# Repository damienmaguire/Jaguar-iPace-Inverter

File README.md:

# Jaguar-iPace-Inverter
Design of Opensource Logic boards to run the Jaguar iPace Inverter and Motors.

PCB Designs in Kicad 9 format.

Front inverter used in the iPace is acuallly a Vitesco EPF2.8+ :
https://vitesco-technologies.com/en/Home/Solutions/Products/High-Voltage-Inverter-(EPF2-8-)-en

Reverse engineering thread on the openinverter forum :
https://openinverter.org/forum/viewtopic.php?f=23&t=1210

Videos :
https://youtu.be/Kg5qWuOF9P8

10/10/25 : Add prelim front drive unit V1 board design (work in progress).

25/03/26 : PCB Layout in progress.

28/03/26 : Layout done. First prototypes ordered from JLCPCB.

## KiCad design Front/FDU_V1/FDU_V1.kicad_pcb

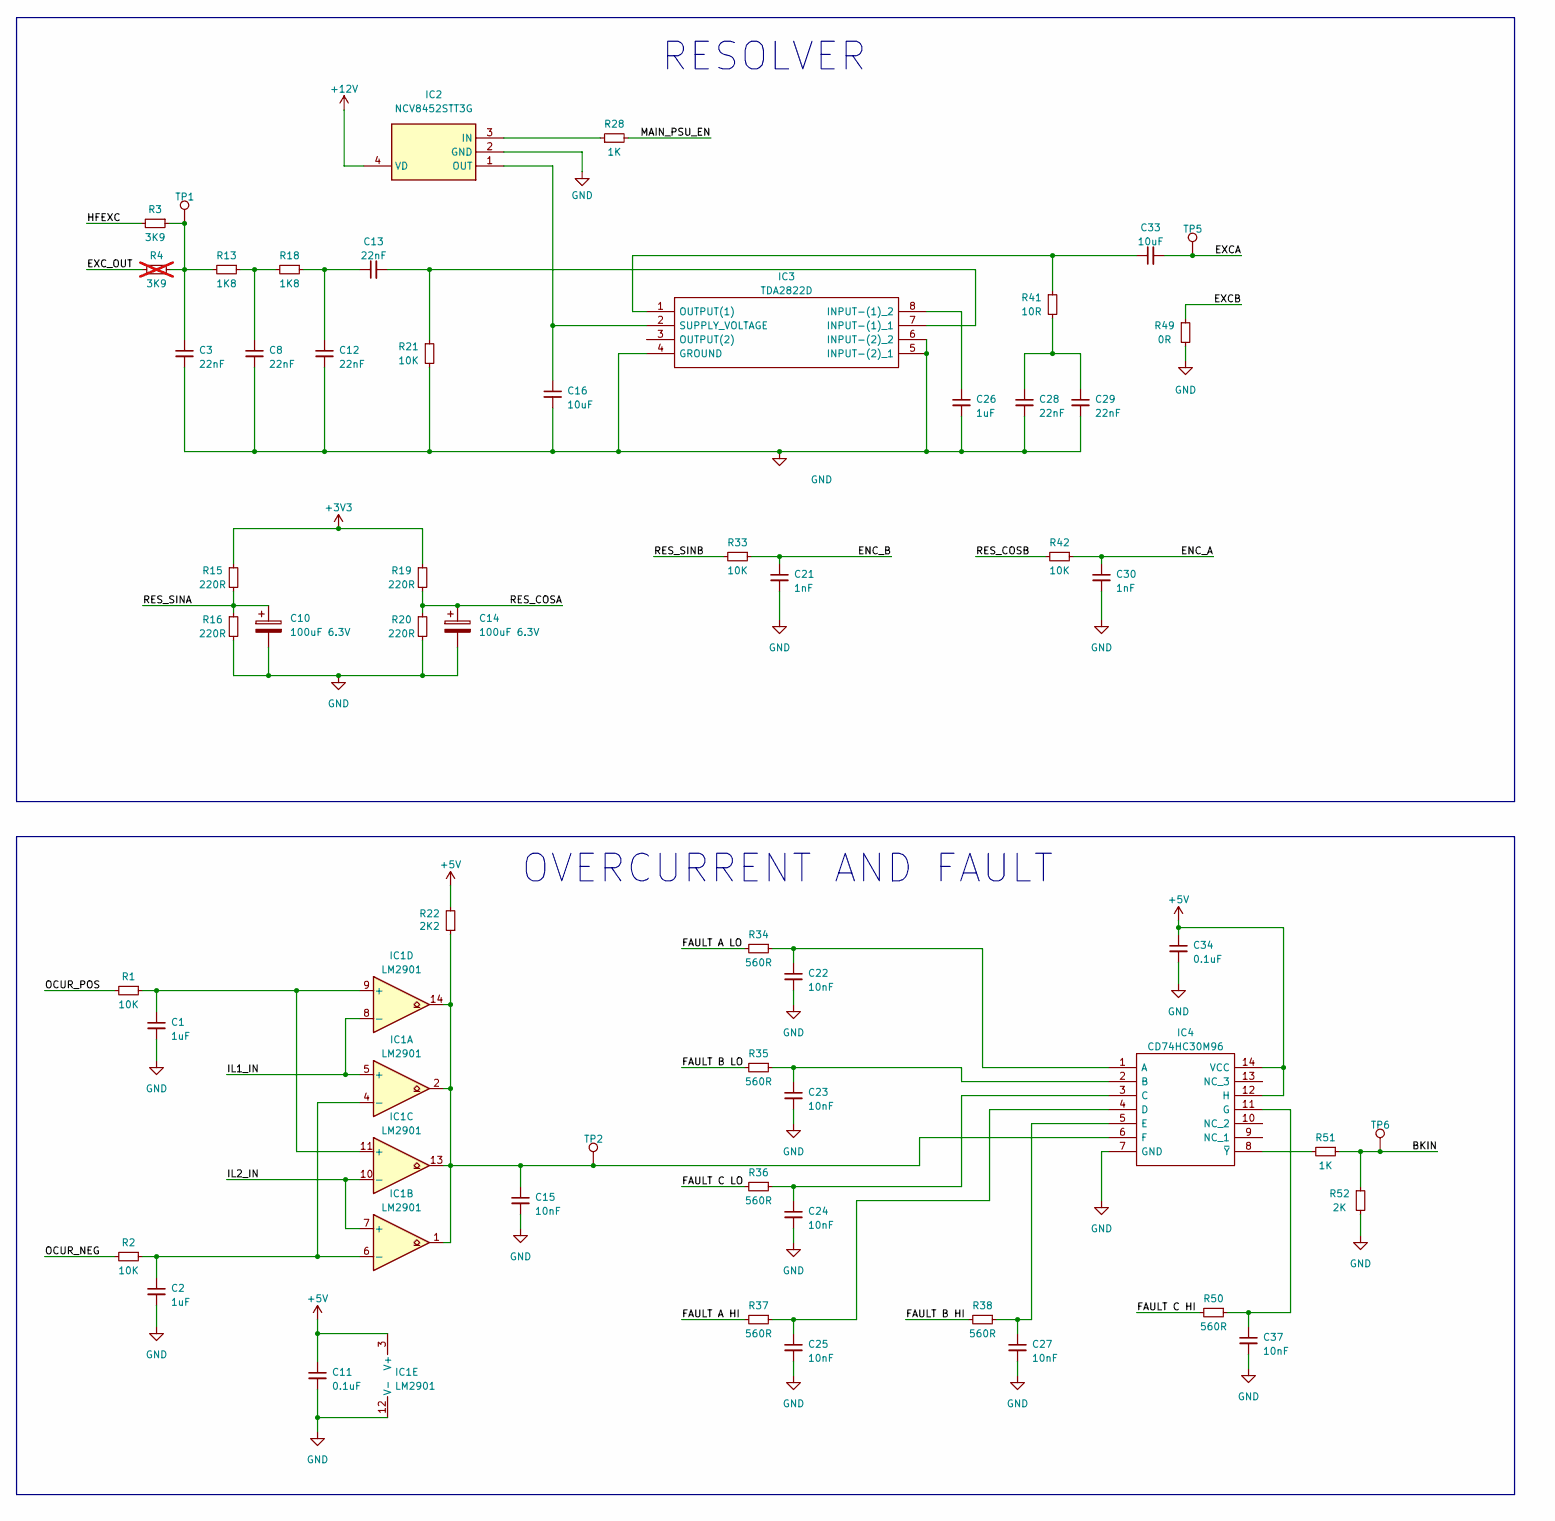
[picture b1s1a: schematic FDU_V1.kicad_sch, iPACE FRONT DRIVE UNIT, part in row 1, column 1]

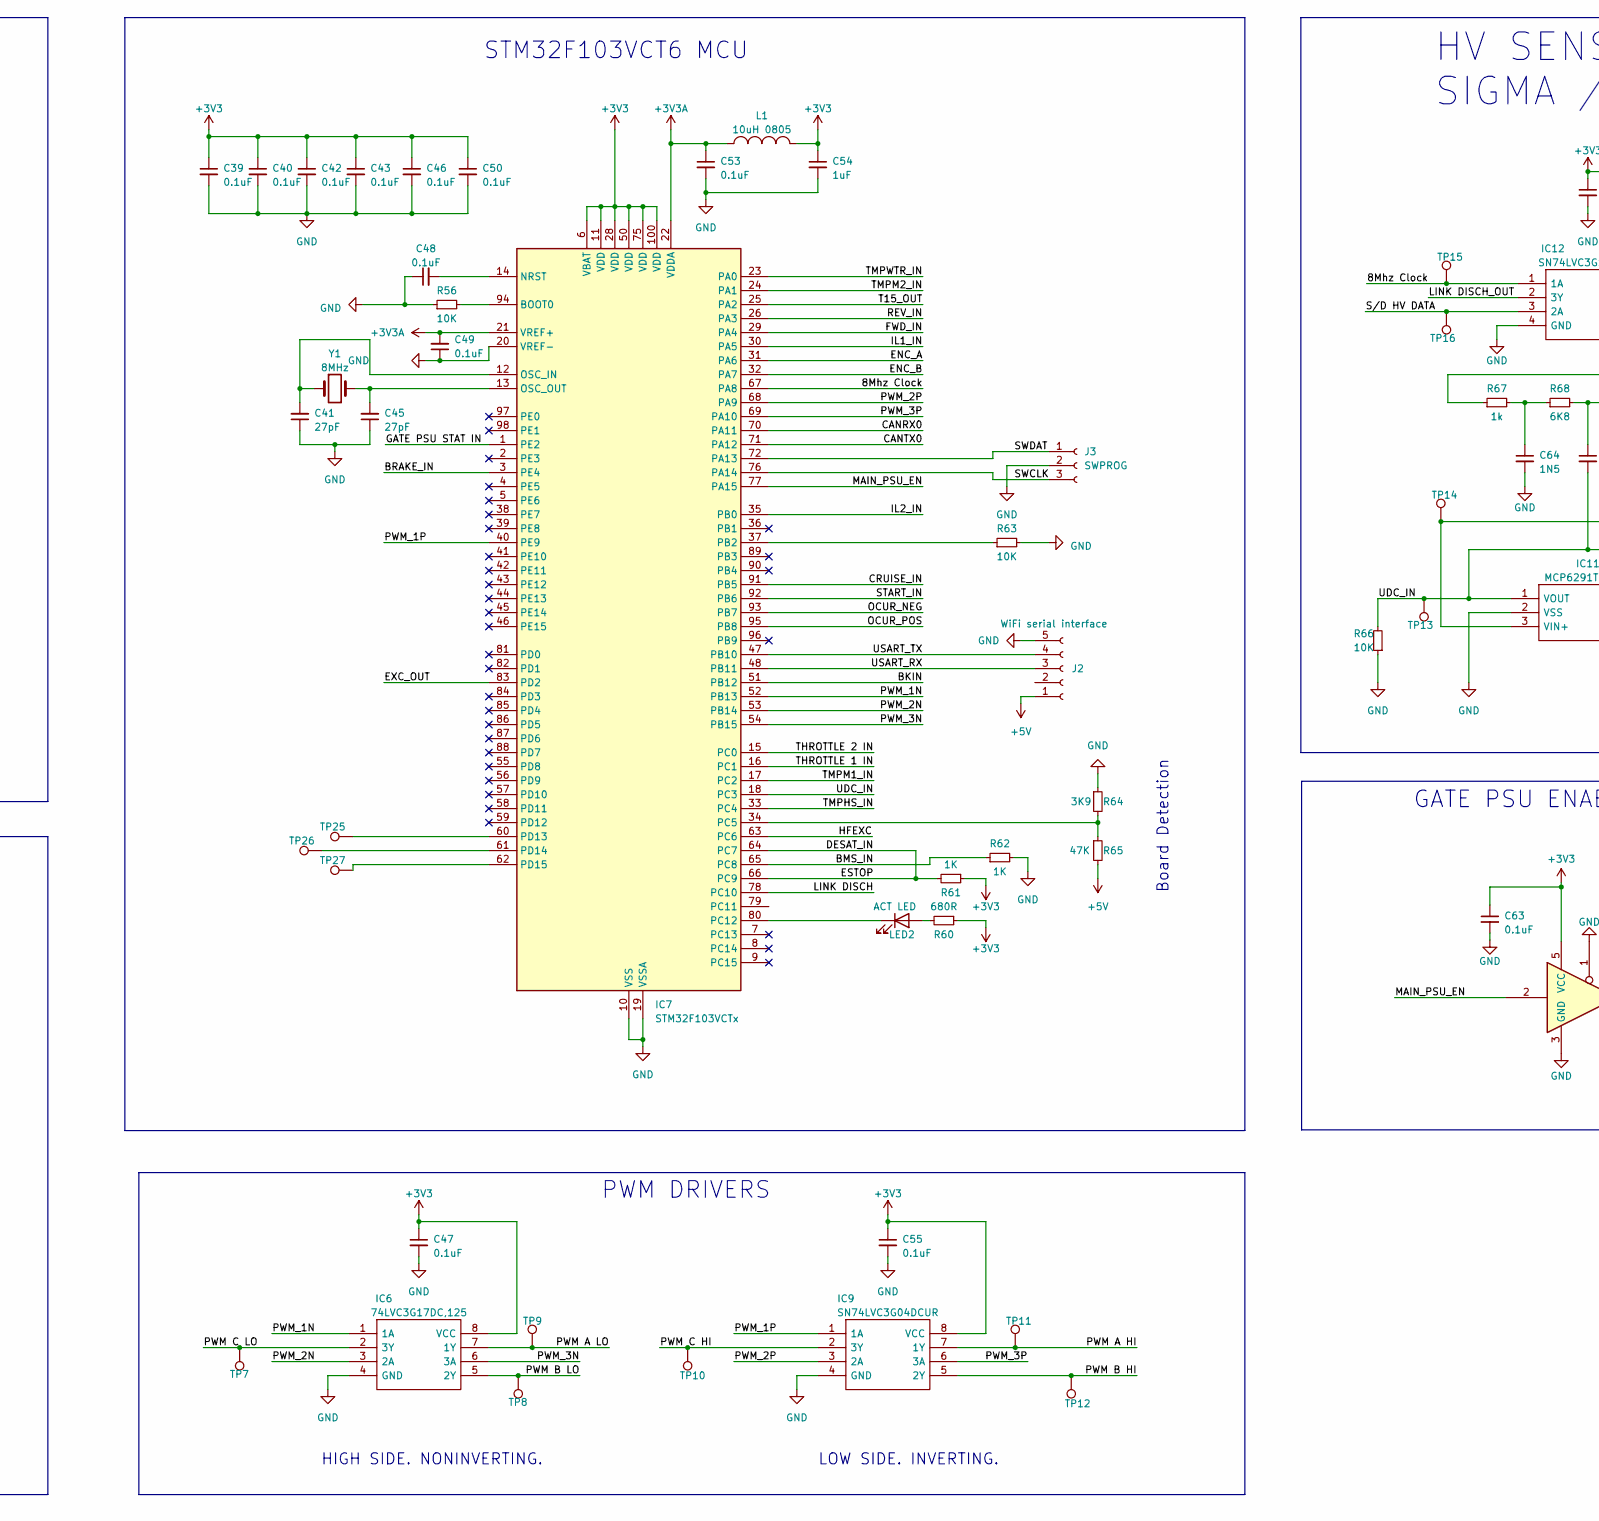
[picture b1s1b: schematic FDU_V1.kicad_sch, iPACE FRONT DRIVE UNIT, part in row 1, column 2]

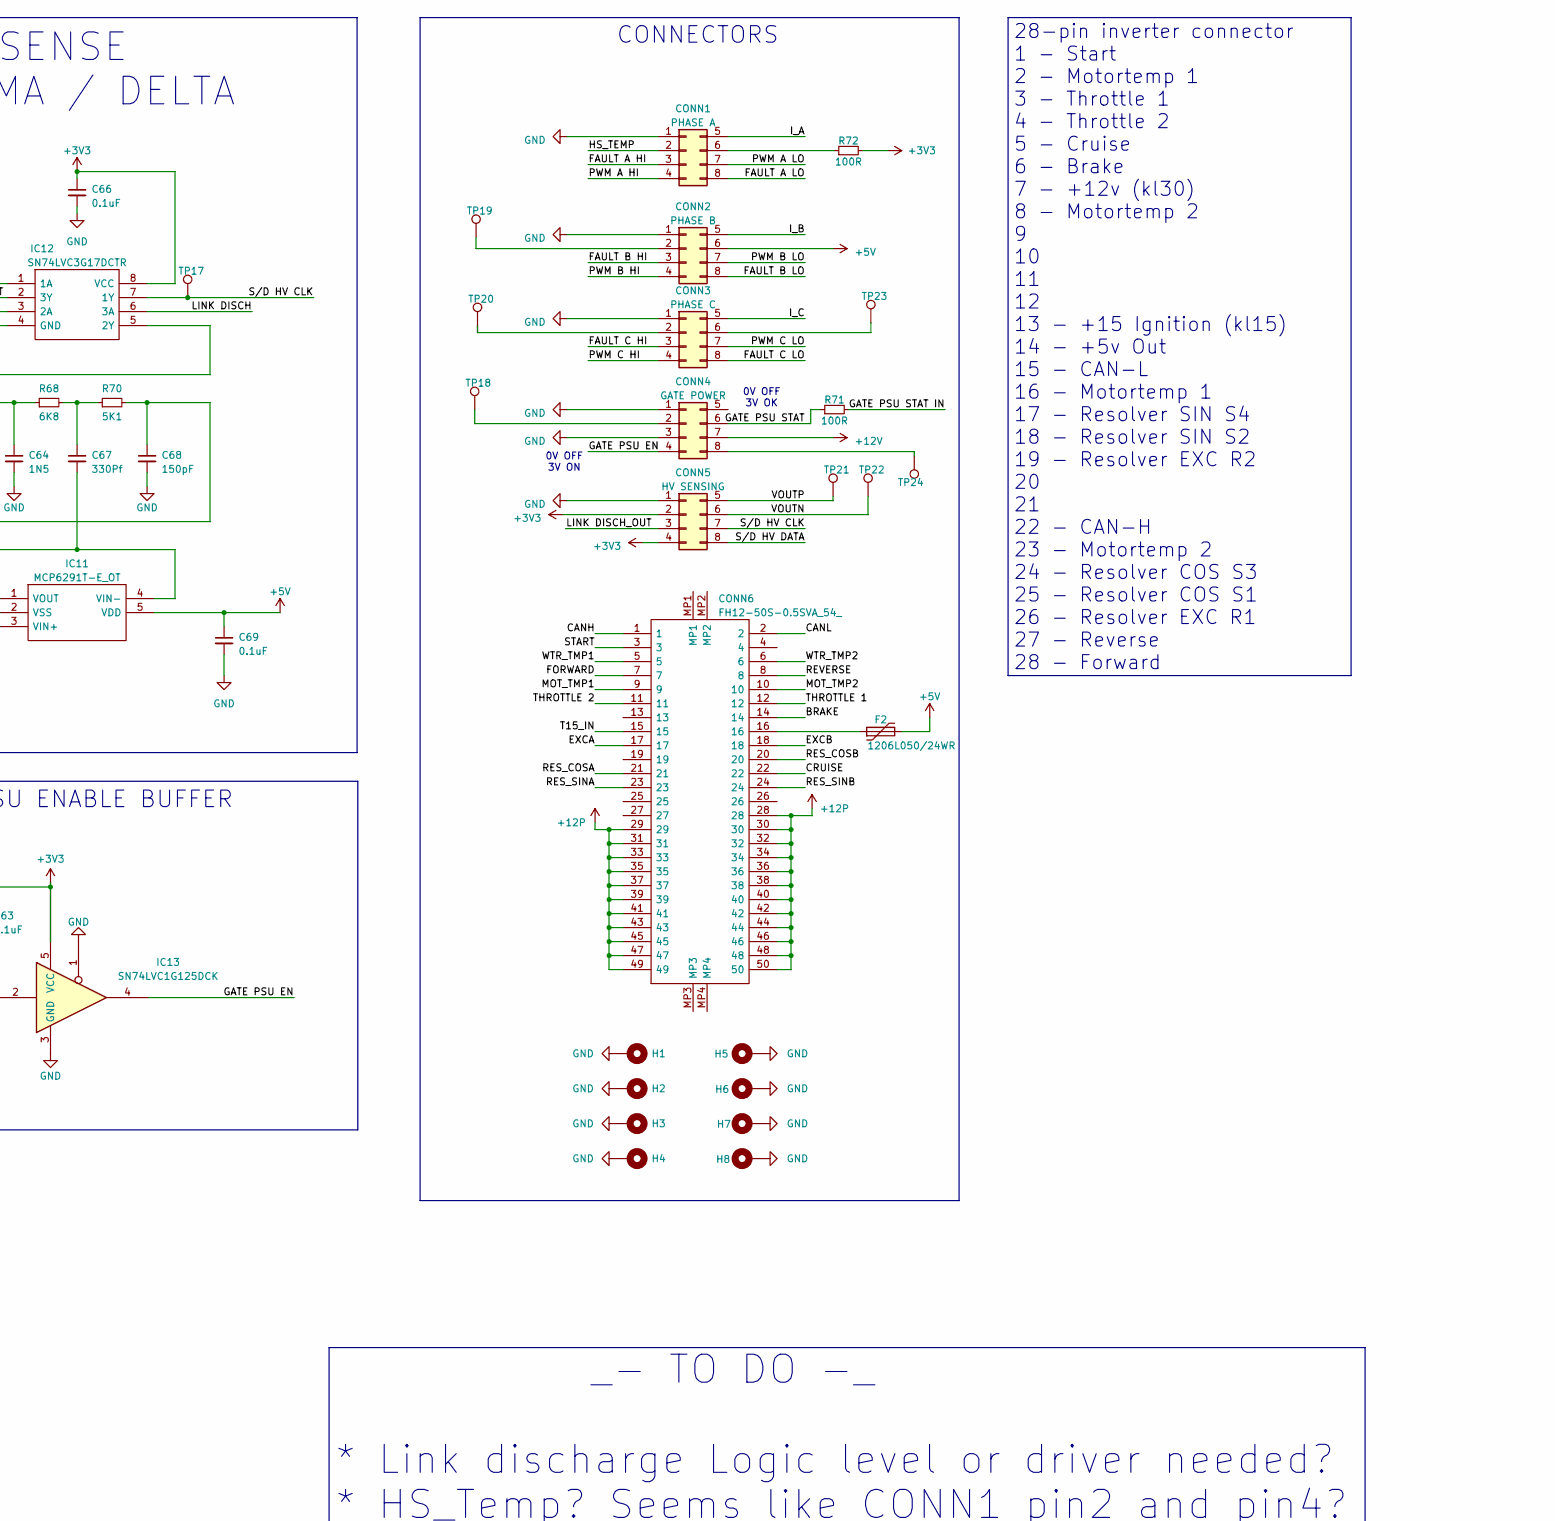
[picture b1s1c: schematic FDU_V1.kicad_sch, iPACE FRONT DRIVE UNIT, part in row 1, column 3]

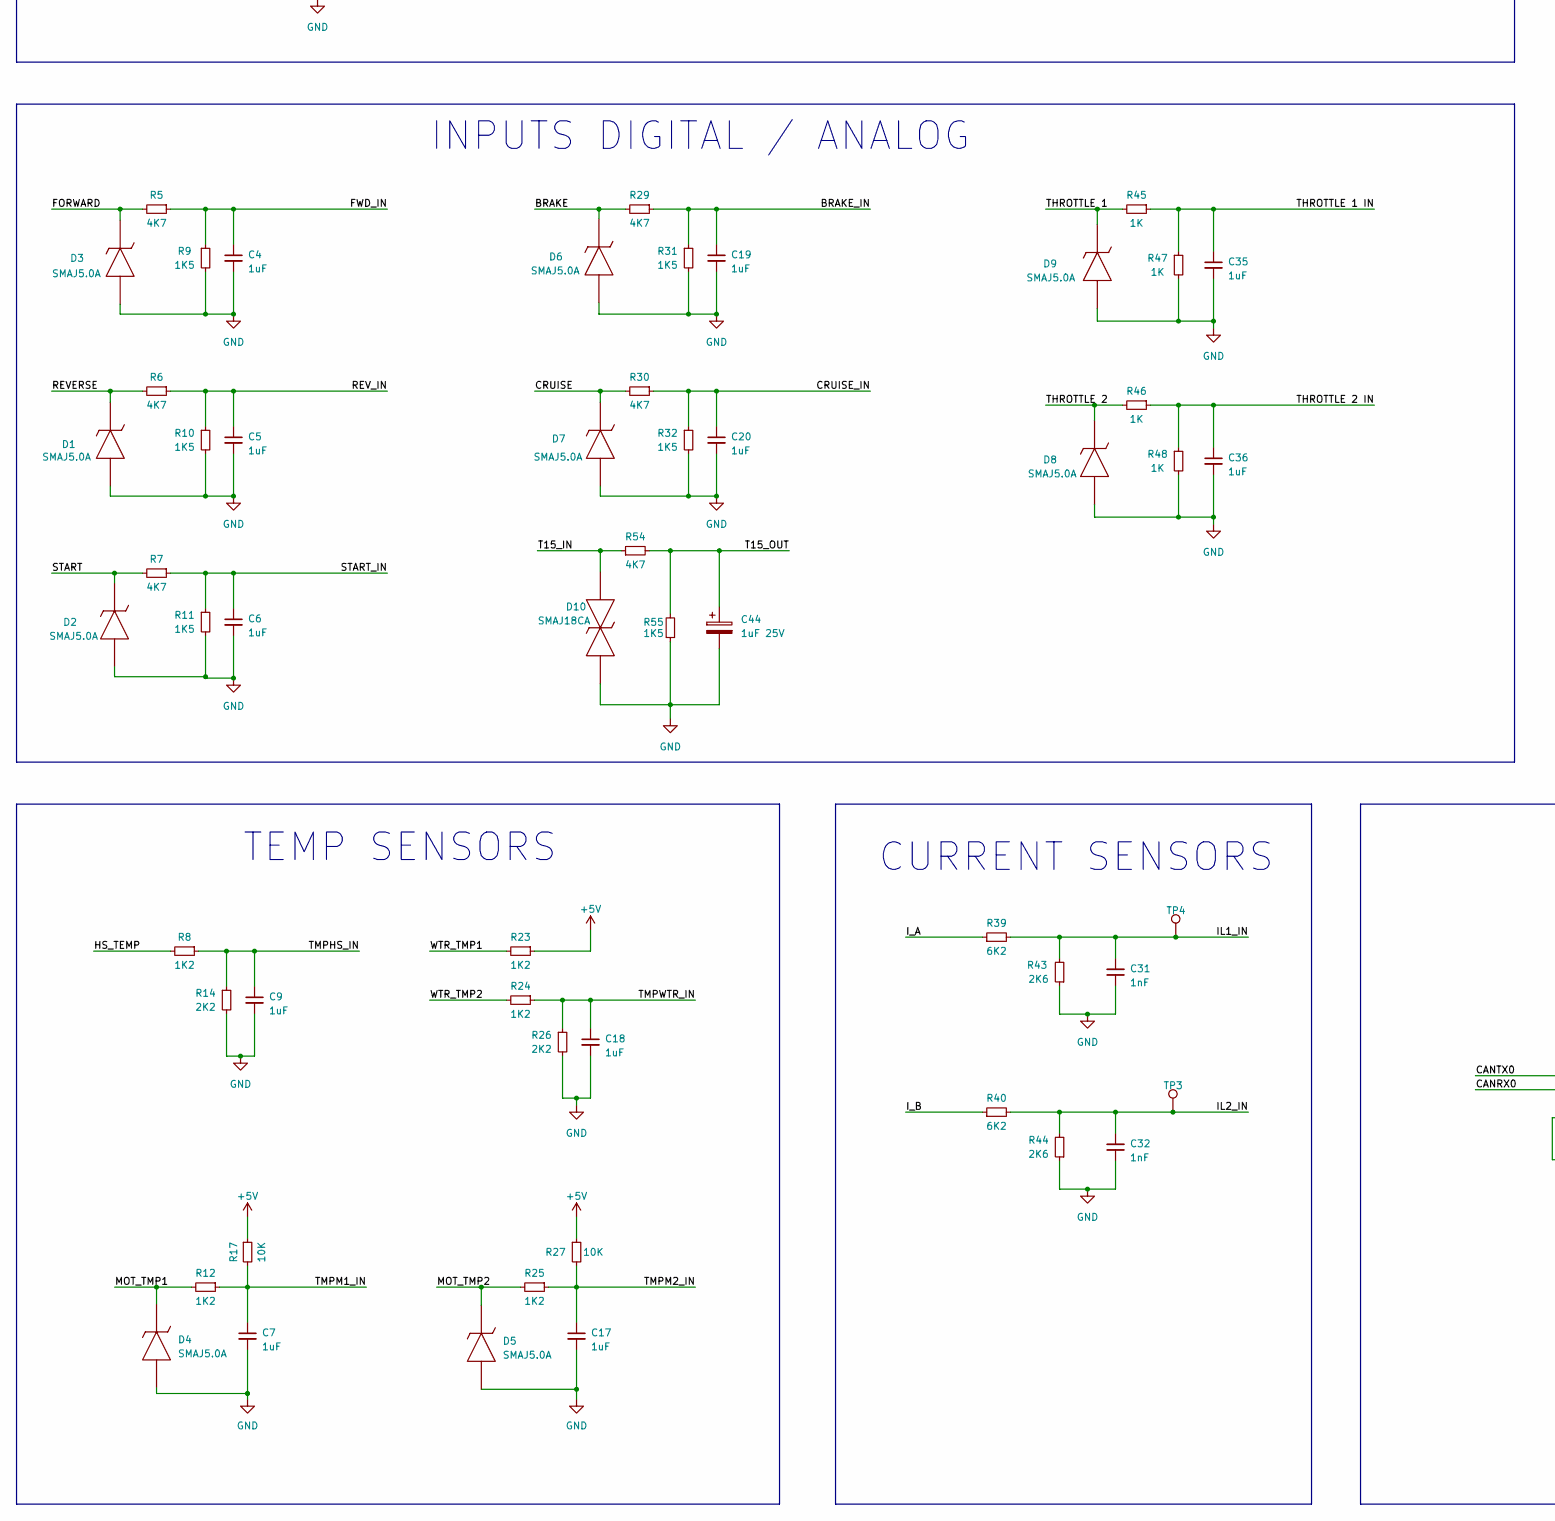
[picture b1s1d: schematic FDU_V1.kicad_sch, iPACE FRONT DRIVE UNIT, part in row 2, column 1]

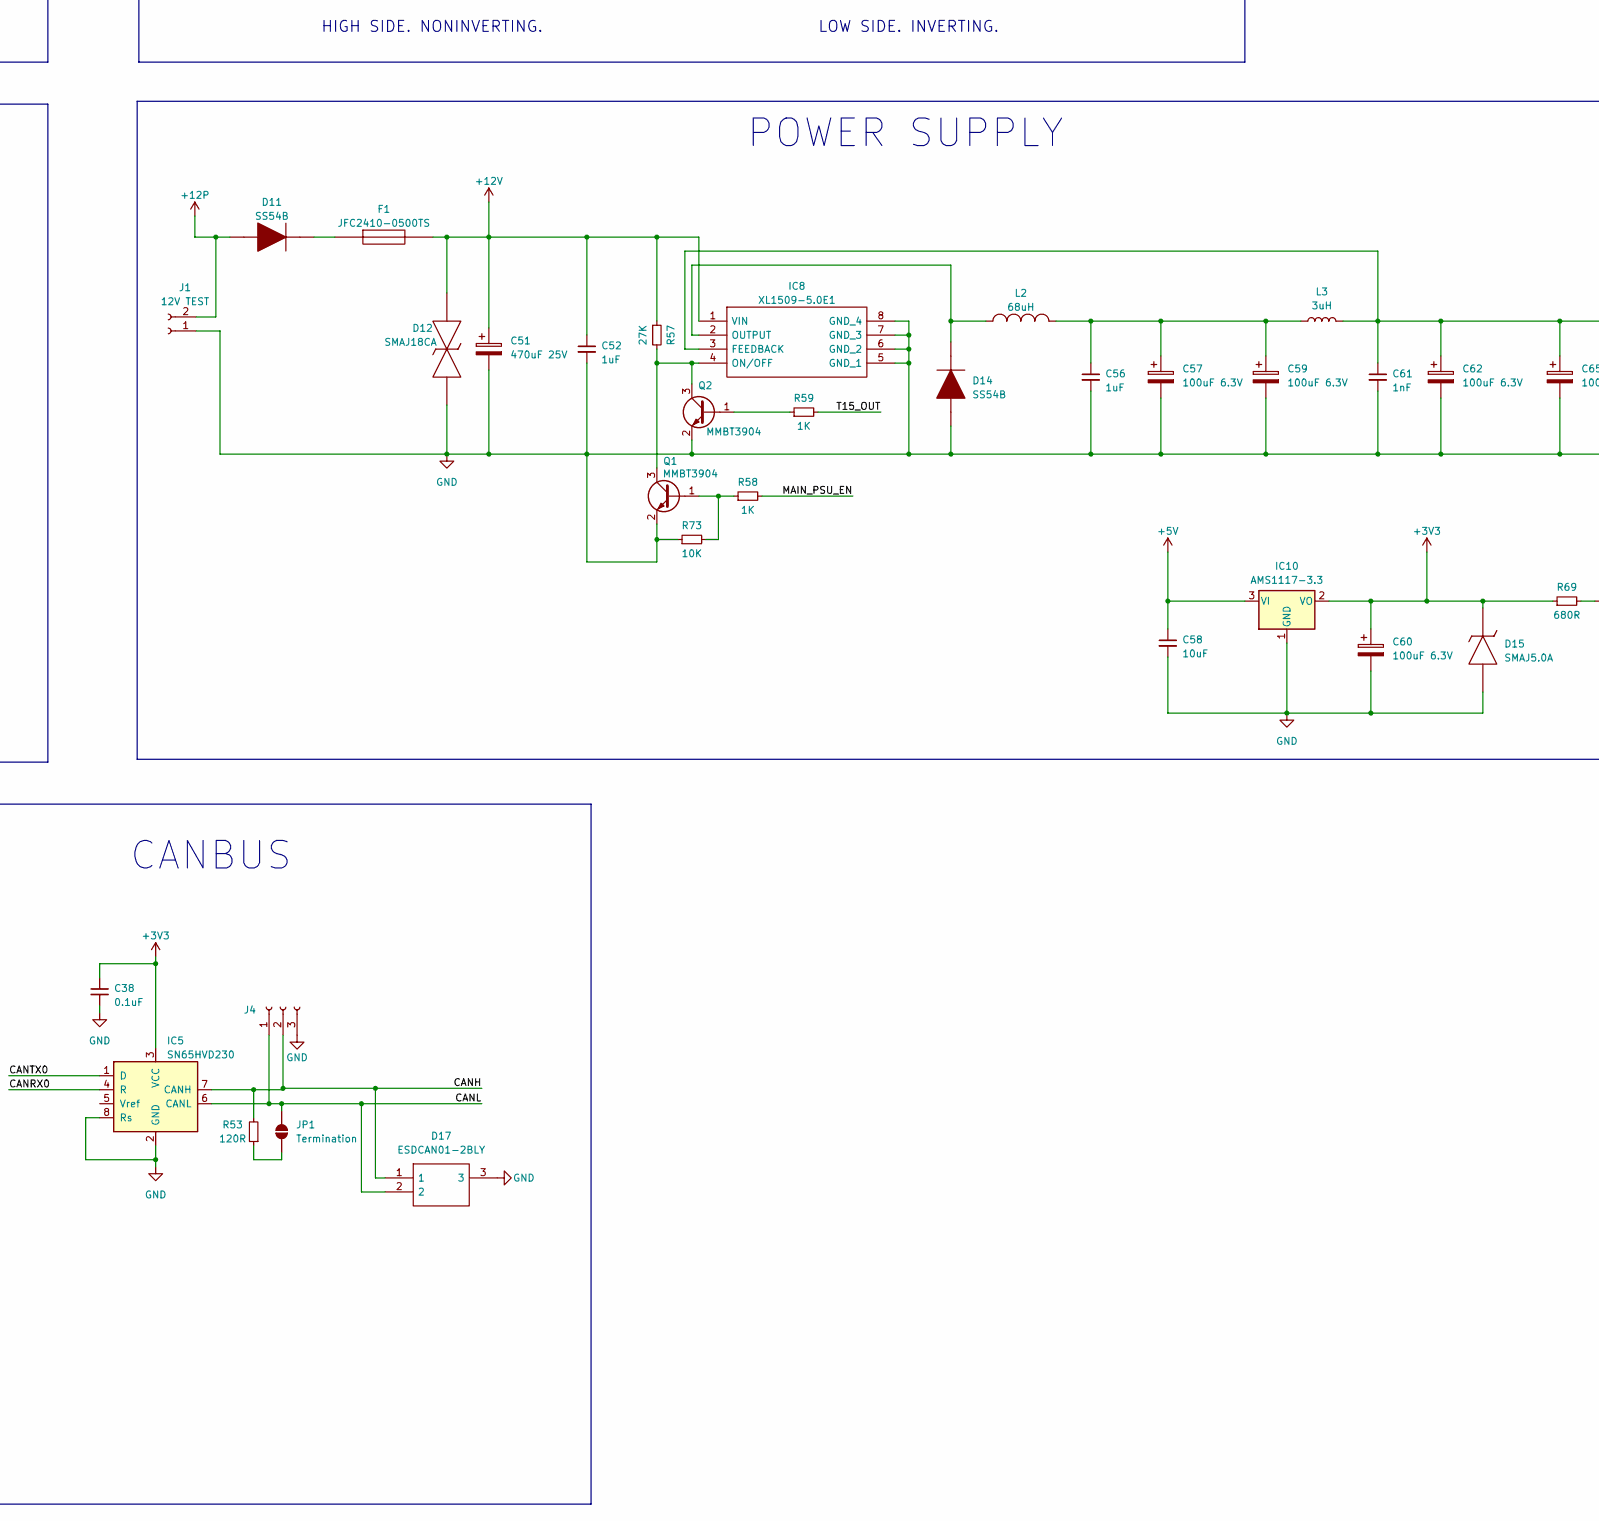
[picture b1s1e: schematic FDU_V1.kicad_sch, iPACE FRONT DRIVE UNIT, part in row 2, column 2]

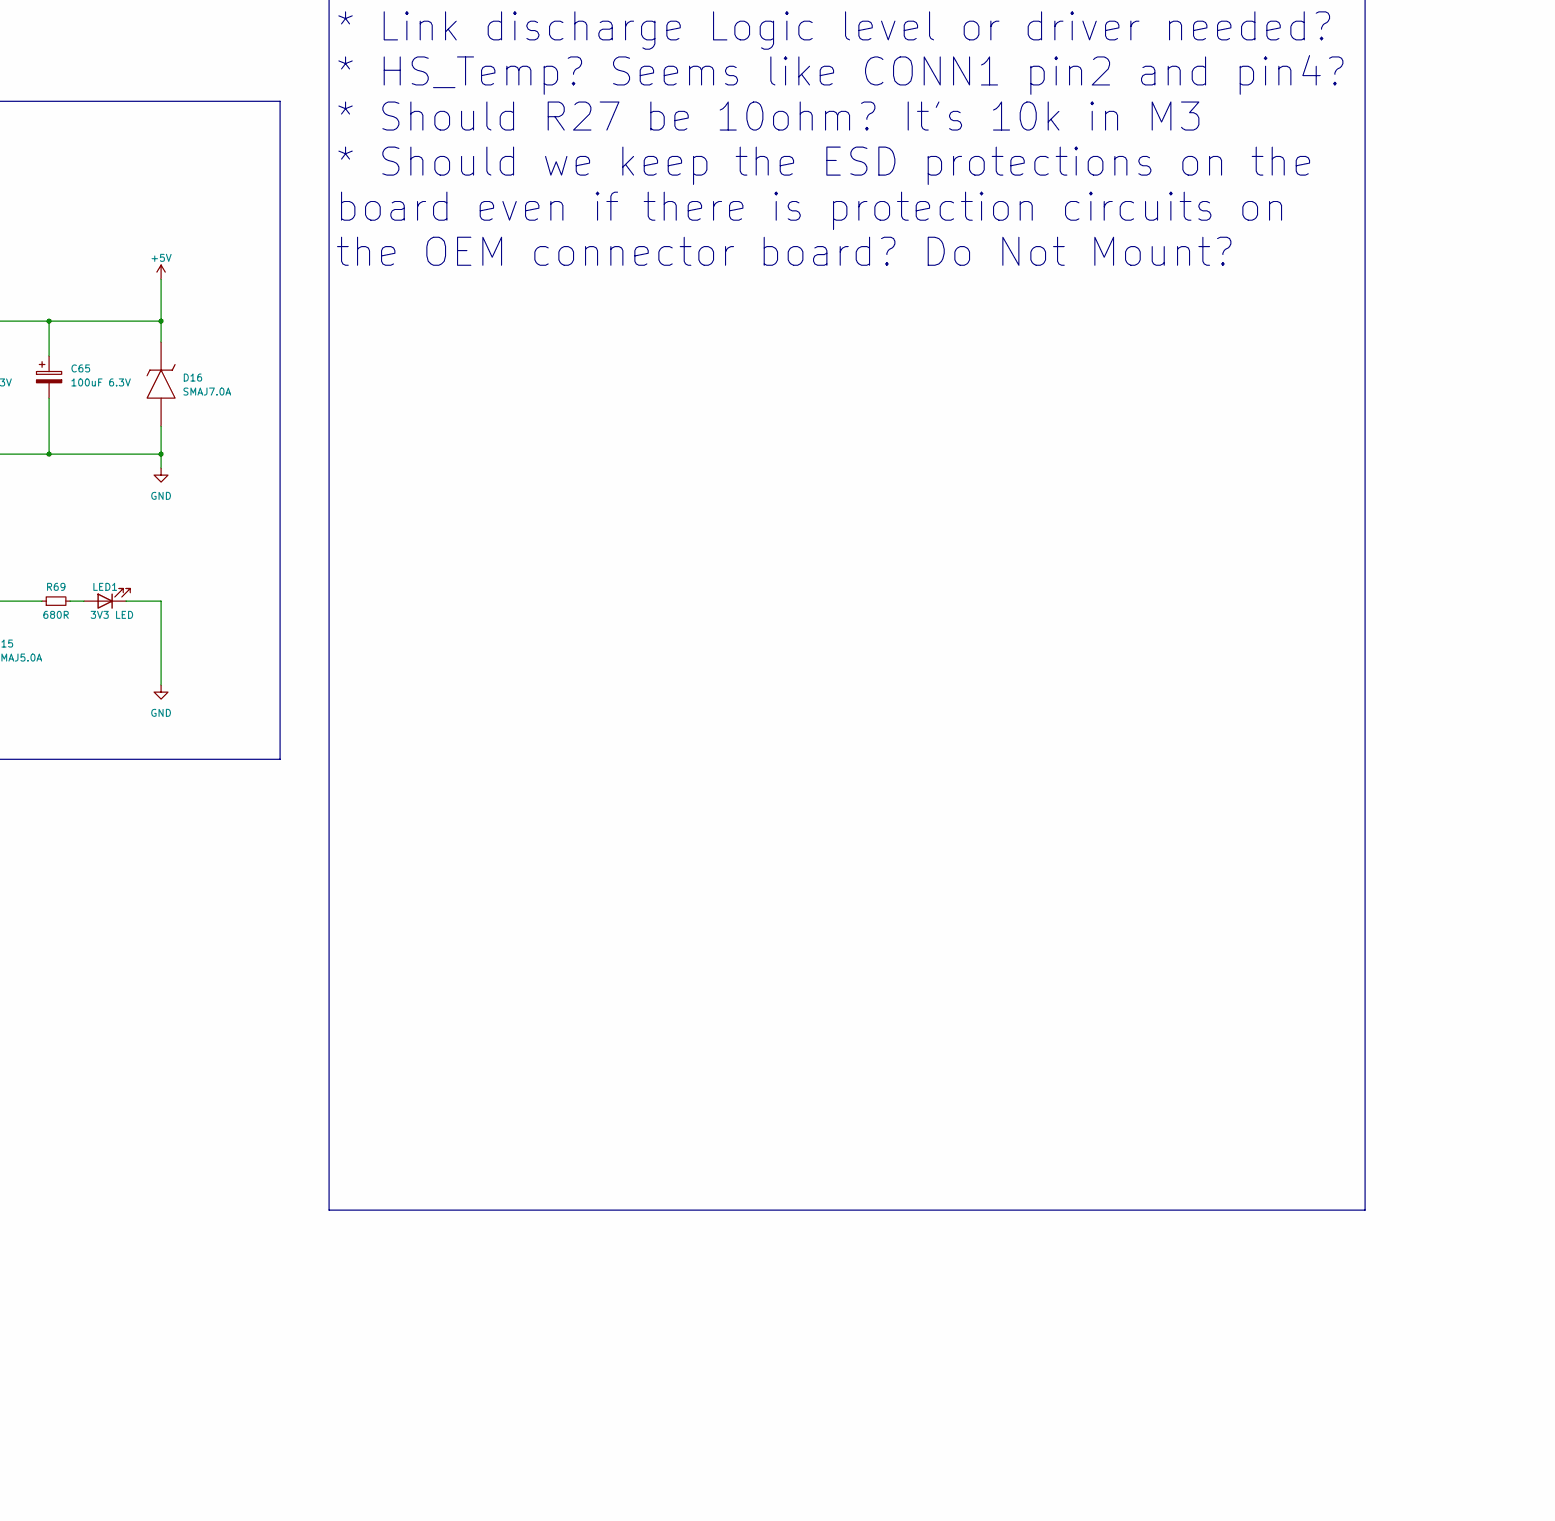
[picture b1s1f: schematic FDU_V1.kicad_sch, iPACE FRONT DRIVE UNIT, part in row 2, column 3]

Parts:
C1, C2, C4, C5, C6, C7, C9, C17, C18, C19, C20, C26, C35, C36, C52, C54, C56: 1uF; C_0805_2012Metric
C3, C8, C12, C13, C28, C29: 22nF; C_0805_2012Metric
C10, C14, C57, C59, C60, C62, C65: 100uF 6.3V; CP_EIA-3528-15_AVX-H
C11, C34, C38, C39, C40, C42, C43, C46, C47, C48, C49, C50, C53, C55, C63, C66, C69: 0.1uF; C_0805_2012Metric
C15, C22, C23, C24, C25, C27, C37: 10nF; C_0805_2012Metric
C16, C33, C58: 10uF; C_0805_2012Metric
C21, C30, C31, C32, C61: 1nF; C_0805_2012Metric
C41, C45: 27pF; C_0805_2012Metric
C44: 1uF 25V; C_0805_2012Metric
C51: 470uF 25V; CP_Elec_10x10
C64: 1N5; C_0805_2012Metric
C67: 330Pf; C_0805_2012Metric
C68: 150pF; C_0805_2012Metric
CONN1: PHASE A; PinHeader_2x04_P2.54mm_Vertical
CONN2: PHASE B; PinHeader_2x04_P2.54mm_Vertical
CONN3: PHASE C; PinHeader_2x04_P2.54mm_Vertical
CONN4: GATE POWER; PinHeader_2x04_P2.54mm_Vertical
CONN5: HV SENSING; PinHeader_2x04_P2.54mm_Vertical
CONN6: FH12-50S-0.5SVA_54_; FH1250S05SVA54; Manufacturer_Part_Number FH12-50S-0.5SVA(54); Mouser Part Number 798-FH1250S0.5SVA54
D1, D2, D3, D4, D5, D6, D7, D8, D9, D15: SMAJ5.0A; DIOM5127X229N; Manufacturer_Part_Number SMAJ5.0A; Mouser Part Number 78-SMAJ5.0A
D10, D12: SMAJ18CA; DIONM5127X229N; Manufacturer_Part_Number SMAJ18CA; Mouser Part Number 652-SMAJ18CA
D11, D14: SS54B; DIOM5336X244N; Manufacturer_Part_Number SS54B
D16: SMAJ7.0A; DIOM5026X229N; Manufacturer_Part_Number SMAJ7.0A; Mouser Part Number 576-SMAJ7.0A
D17: ESDCAN01-2BLY; SOT95P255X150-3N; Manufacturer_Part_Number ESDCAN01-2BLY; Mouser Part Number 511-ESDCAN01-2BLY
F1: JFC2410-0500TS; FUSC6126X280N; Manufacturer_Part_Number JFC2410-0500TS
F2: 1206L050/24WR; Fuse_1206_3216Metric
H1, H2, H3, H4, H5, H6, H7, H8: MountingHole; MountingHole_8mm_ipace
IC1: LM2901; SOIC-14_3.9x8.7mm_P1.27mm
IC2: NCV8452STT3G; SOT230P700X180-4N; Manufacturer_Part_Number NCV8452STT3G; Mouser Part Number 863-NCV8452STT3G
IC3: TDA2822D; SOIC127P600X175-8N; Manufacturer_Part_Number TDA2822D; Mouser Part Number 511-TDA2822D
IC4: CD74HC30M96; SOIC127P600X175-14N; Manufacturer_Part_Number CD74HC30M96; Mouser Part Number 595-CD74HC30M96
IC5: SN65HVD230; SOIC-8_3.9x4.9mm_P1.27mm
IC6: 74LVC3G17DC,125; SOP50P310X100-8N; Manufacturer_Part_Number 74LVC3G17DC,125; Mouser Part Number 771-LVC3G17DC125
IC7: STM32F103VCTx; LQFP-100_14x14mm_P0.5mm
IC8: XL1509-5.0E1; SOIC127P600X175-8N; Manufacturer_Part_Number XL1509-5.0E1
IC9: SN74LVC3G04DCUR; SOP50P310X90-8N; Manufacturer_Part_Number SN74LVC3G04DCUR; Mouser Part Number 595-SN74LVC3G04DCUR
IC10: AMS1117-3.3; SOT-223-3_TabPin2
IC11: MCP6291T-E_OT; SOT95P280X145-5N; Manufacturer_Part_Number MCP6291T-E/OT; Mouser Part Number 579-MCP6291T-E/OT
IC12: SN74LVC3G17DCTR; MSOP-8_3x3mm_P0.65mm; Manufacturer_Part_Number 74LVC3G17DC,125; Mouser Part Number 771-LVC3G17DC125
IC13: SN74LVC1G125DCK; Texas_R-PDSO-G5_DCK-5
J1: 12V TEST; PinHeader_1x02_P2.54mm_Vertical
J2: WiFi serial interface; PinHeader_1x05_P2.54mm_Vertical
J3, J4: SWPROG; PinHeader_1x03_P2.54mm_Vertical
JP1: Termination; SolderJumper-2_P1.3mm_Open_RoundedPad1.0x1.5mm
L1: 10uH 0805; L_0805_2012Metric
L2: 68uH; L_12x12mm_H8mm
L3: 3uH; L_10.4x10.4_H4.8
LED1: 3V3 LED; LED_0805_2012Metric
LED2: ACT LED; LED_0805_2012Metric
Q1, Q2: MMBT3904; SOT-23
R1, R2, R17, R21, R27, R33, R42, R56, R63, R66, R73: 10K; R_0805_2012Metric
R3, R64: 3K9; R_0805_2012Metric
R4: 3K9; R_0805_2012Metric; not fitted
R5, R6, R7, R29, R30, R54: 4K7; R_0805_2012Metric
R8, R12, R23, R24, R25: 1K2; R_0805_2012Metric
R9, R10, R11, R31, R32, R55: 1K5; R_0805_2012Metric
R13, R18: 1K8; R_0805_2012Metric
R14, R22, R26: 2K2; R_0805_2012Metric
R15, R16, R19, R20: 220R; R_0805_2012Metric
R28, R45, R46, R47, R48, R51, R58, R59, R61, R62: 1K; R_0805_2012Metric
R34, R35, R36, R37, R38, R50: 560R; R_0805_2012Metric
R39, R40: 6K2; R_0805_2012Metric
R41: 10R; R_0805_2012Metric
R43, R44: 2K6; R_0805_2012Metric
R49: 0R; R_0805_2012Metric
R52: 2K; R_0805_2012Metric
R53: 120R; R_0805_2012Metric
R57: 27K; R_0805_2012Metric
R60, R69: 680R; R_0805_2012Metric
R65: 47K; R_0805_2012Metric
R67: 1k; R_0805_2012Metric
R68: 6K8; R_0805_2012Metric
R70: 5K1; R_0805_2012Metric
R71, R72: 100R; R_0805_2012Metric
TP1, TP2, TP3, TP4, TP5, TP6, TP7, TP8, TP9, TP10, TP11, TP12, TP13, TP14, TP15, TP16, TP17, TP18, TP19, TP20, TP21, TP22, TP23, TP24, TP25, TP26, TP27: TestPoint; TestPoint_Loop_D2.50mm_Drill1.0mm
Y1: 8MHz; Crystal_SMD_5032-2Pin_5.0x3.2mm

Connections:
+3V3: C38.1, C39.1, C40.1, C42.1, C43.1, C46.1, C47.1, C50.1, C54.1, C55.1, C60.1, C63.1, C66.1, CONN5.2, CONN5.4, D15.1, IC5.3 (VCC), IC6.8 (VCC), IC7.6 (VBAT), IC7.11 (VDD), IC7.28 (VDD), IC7.50 (VDD), IC7.75 (VDD), IC7.100 (VDD), IC9.8 (VCC), IC10.2 (VO), IC12.8 (VCC), IC13.5 (VCC), L1.2, R15.1, R19.1, R60.1, R61.1, R69.1, R72.2
+3V3A: C49.2, C53.1, IC7.21 (VREF+), IC7.22 (VDDA), L1.1
+5V: C11.1, C34.1, C58.1, C61.1, C62.1, C65.1, C69.1, CONN2.6, D16.1, F2.2, IC1.3 (V+), IC4.12 (H), IC4.14 (VCC), IC8.3 (FEEDBACK), IC10.3 (VI), IC11.5 (VDD), J2.1, L3.2, R17.1, R22.2, R23.1, R27.1, R65.2
+12P: CONN6.28, CONN6.29, CONN6.30, CONN6.31, CONN6.32, CONN6.33, CONN6.34, CONN6.35, CONN6.36, CONN6.37, CONN6.38, CONN6.39, CONN6.40, CONN6.41, CONN6.42, CONN6.43, CONN6.44, CONN6.45, CONN6.46, CONN6.47, CONN6.48, CONN6.49, CONN6.50, D11.2, J1.2
+12V: C51.1, C52.1, CONN4.7, D12.1, F1.2, IC2.4 (VD), IC8.1 (VIN), R57.1
/8Mhz Clock: IC7.67 (PA8), IC12.1 (1A), TP15.1
/BKIN: IC7.51 (PB12), R51.1, R52.1, TP6.1
/BMS_IN: IC7.65 (PC8), R62.1
/BRAKE: CONN6.14, D6.1, R29.2
/BRAKE_IN: C19.1, IC7.3 (PE4), R29.1, R31.1
/CANH: CONN6.1, D17.1, IC5.7 (CANH), J4.2, R53.2
/CANL: CONN6.2, D17.2, IC5.6 (CANL), J4.1, JP1.2 (B)
/CANRX0: IC5.4 (R), IC7.70 (PA11)
/CANTX0: IC5.1 (D), IC7.71 (PA12)
/CRUISE: CONN6.22, D7.1, R30.2
/CRUISE_IN: C20.1, IC7.91 (PB5), R30.1, R32.1
/DESAT_IN: IC7.64 (PC7), IC7.66 (PC9), R61.2
/ENC_A: C30.1, IC7.31 (PA6), R42.1
/ENC_B: C21.1, IC7.32 (PA7), R33.1
/EXCA: C33.2, CONN6.17, TP5.1
/EXCB: CONN6.18, R49.1
/EXC_OUT: IC7.83 (PD2), R4.2
/FAULT A HI: CONN1.3, R37.2
/FAULT A LO: CONN1.8, R34.2
/FAULT B HI: CONN2.3, R38.2
/FAULT B LO: CONN2.8, R35.2
/FAULT C HI: CONN3.3, R50.2
/FAULT C LO: CONN3.8, R36.2
/FORWARD: CONN6.7, D3.1, R5.2
/FWD_IN: C4.1, IC7.29 (PA4), R5.1, R9.1
/GATE PSU EN: CONN4.4, IC13.4
/GATE PSU STAT: CONN4.6, R71.1
/GATE PSU STAT IN: IC7.1 (PE2), R71.2
/HFEXC: IC7.63 (PC6), R3.2
/HS_TEMP: CONN1.2, R8.2
/IL1_IN: C31.2, IC1.5 (+), IC1.8 (-), IC7.30 (PA5), R39.2, R43.2, TP4.1
/IL2_IN: C32.2, IC1.7 (+), IC1.10 (-), IC7.35 (PB0), R40.2, R44.2, TP3.1
/I_A: CONN1.5, R39.1
/I_B: CONN2.5, R40.1
/I_C: CONN3.5
/LINK DISCH: IC7.78 (PC10), IC12.6 (3A)
/LINK DISCH_OUT: CONN5.3, IC12.2 (3Y)
/MAIN_PSU_EN: IC7.77 (PA15), IC13.2, R28.2, R58.2
/MOT_TMP1: CONN6.9, D4.1, R12.2
/MOT_TMP2: CONN6.10, D5.1, R25.2
/OCUR_NEG: IC7.93 (PB7), R2.2
/OCUR_POS: IC7.95 (PB8), R1.2
/PWM A HI: CONN1.4, IC9.7 (1Y), TP11.1
/PWM A LO: CONN1.7, IC6.7 (1Y), TP9.1
/PWM B HI: CONN2.4, IC9.5 (2Y), TP12.1
/PWM B LO: CONN2.7, IC6.5 (2Y), TP8.1
/PWM C HI: CONN3.4, IC9.2 (3Y), TP10.1
/PWM C LO: CONN3.7, IC6.2 (3Y), TP7.1
/PWM_1N: IC6.1 (1A), IC7.52 (PB13)
/PWM_1P: IC7.40 (PE9), IC9.1 (1A)
/PWM_2N: IC6.3 (2A), IC7.53 (PB14)
/PWM_2P: IC7.68 (PA9), IC9.3 (2A)
/PWM_3N: IC6.6 (3A), IC7.54 (PB15)
/PWM_3P: IC7.69 (PA10), IC9.6 (3A)
/RES_COSA: C14.1, CONN6.21, R19.2, R20.1
/RES_COSB: CONN6.20, R42.2
/RES_SINA: C10.1, CONN6.23, R15.2, R16.1
/RES_SINB: CONN6.24, R33.2
/REVERSE: CONN6.8, D1.1, R6.2
/REV_IN: C5.1, IC7.26 (PA3), R6.1, R10.1
/START: CONN6.3, D2.1, R7.2
/START_IN: C6.1, IC7.92 (PB6), R7.1, R11.1
/SWCLK: IC7.76 (PA14), J3.3
/SWDAT: IC7.72 (PA13), J3.1
/S/D HV CLK: CONN5.7, IC12.7 (1Y), TP17.1
/S/D HV DATA: CONN5.8, IC12.3 (2A), TP16.1
/T15_IN: CONN6.15, D10.1, R54.1
/T15_OUT: C44.1, IC7.25 (PA2), R54.2, R55.2, R59.2
/THROTTLE 1: CONN6.12, D9.1, R45.2
/THROTTLE 1 IN: C35.1, IC7.16 (PC1), R45.1, R47.1
/THROTTLE 2: CONN6.11, D8.1, R46.2
/THROTTLE 2 IN: C36.1, IC7.15 (PC0), R46.1, R48.1
/TMPHS_IN: C9.1, IC7.33 (PC4), R8.1, R14.1
/TMPM1_IN: C7.1, IC7.17 (PC2), R12.1, R17.2
/TMPM2_IN: C17.1, IC7.24 (PA1), R25.1, R27.2
/TMPWTR_IN: C18.1, IC7.23 (PA0), R24.1, R26.1
/UDC_IN: C67.2, IC7.18 (PC3), IC11.1 (VOUT), IC11.4 (VIN-), R66.2, TP13.1
/USART_RX: IC7.48 (PB11), J2.3
/USART_TX: IC7.47 (PB10), J2.4
/VOUTN: CONN5.6, TP22.1
/VOUTP: CONN5.5, TP21.1
/WTR_TMP1: CONN6.5, R23.2
/WTR_TMP2: CONN6.6, R24.2
GND: C1.2, C2.2, C3.2, C4.2, C5.2, C6.2, C7.2, C8.2, C9.2, C10.2, C11.2, C12.2, C14.2, C15.2, C16.2, C17.2, C18.2, C19.2, C20.2, C21.2, C22.2, C23.2, C24.2, C25.2, C26.2, C27.2, C28.2, C29.2, C30.2, C31.1, C32.1, C34.2, C35.2, C36.2, C37.2, C38.2, C39.2, C40.2, C41.1, C42.2, C43.2, C44.2, C45.1, C46.2, C47.2, C48.1, C49.1, C50.2, C51.2, C52.2, C53.2, C54.2, C55.2, C56.2, C57.2, C58.2, C59.2, C60.2, C61.2, C62.2, C63.2, C64.2, C65.2, C66.2, C68.2, C69.2, CONN1.1, CONN2.1, CONN3.1, CONN4.1, CONN4.3, CONN5.1, D1.2, D2.2, D3.2, D4.2, D5.2, D6.2, D7.2, D8.2, D9.2, D10.2, D12.2, D14.2, D15.2, D16.2, D17.3, H1.1, H2.1, H3.1, H4.1, H5.1, H6.1, H7.1, H8.1, IC1.12 (V-), IC2.2 (GND), IC3.4 (GROUND), IC3.5 (INPUT-(2)_1), IC3.6 (INPUT-(2)_2), IC4.7 (GND), IC5.2 (GND), IC5.8 (Rs), IC6.4 (GND), IC7.10 (VSS), IC7.19 (VSSA), IC7.20 (VREF-), IC7.27 (VSS), IC7.49 (VSS), IC7.74 (VSS), IC7.99 (VSS), IC8.5 (GND_1), IC8.6 (GND_2), IC8.7 (GND_3), IC8.8 (GND_4), IC9.4 (GND), IC10.1 (GND), IC11.2 (VSS), IC12.4 (GND), IC13.1, IC13.3 (GND), J1.1, J2.5, J3.2, J4.3, LED1.1 (K), Q1.2 (E), Q2.2 (E), R9.2, R10.2, R11.2, R14.2, R16.2, R20.2, R21.2, R26.2, R31.2, R32.2, R43.1, R44.1, R47.2, R48.2, R49.2, R52.2, R55.1, R56.1, R62.2, R63.2, R64.1, R66.1, R73.1
unnamed: C3.1, R3.1, R4.1, R13.2, TP1.1
unnamed: C8.1, R13.1, R18.2
unnamed: C12.1, C13.1, R18.1
unnamed: C28.1, C29.1, R41.2
unnamed: C56.1, C57.1, C59.1, L2.2, L3.1
unnamed: C64.1, R67.2, R68.1
unnamed: C67.1, R68.2, R70.1
unnamed: CONN1.6, R72.1
unnamed: CONN2.2, TP19.1
unnamed: CONN3.2, TP20.1
unnamed: CONN3.6, TP23.1
unnamed: CONN4.2, TP18.1
unnamed: CONN4.8, TP24.1
unnamed: CONN6.16, F2.1
unnamed: D11.1, F1.1
unnamed: C2.1, IC1.4 (-), IC1.6 (-), R2.1
unnamed: C1.1, IC1.9 (+), IC1.11 (+), R1.1
unnamed: IC2.3 (IN), R28.1
unnamed: C16.1, IC2.1 (OUT), IC3.2 (SUPPLY_VOLTAGE)
unnamed: C13.2, IC3.7 (INPUT-(1)_1), R21.1
unnamed: C26.1, IC3.8 (INPUT-(1)_2)
unnamed: C33.1, IC3.1 (OUTPUT(1)), R41.1
unnamed: C22.1, IC4.1 (A), R34.1
unnamed: C23.1, IC4.2 (B), R35.1
unnamed: C24.1, IC4.3 (C), R36.1
unnamed: C25.1, IC4.4 (D), R37.1
unnamed: C27.1, IC4.5 (E), R38.1
unnamed: C15.1, IC1.1, IC1.2, IC1.13, IC1.14, IC4.6 (F), R22.1, TP2.1
unnamed: C37.1, IC4.11 (G), R50.1
unnamed: IC4.8 (~Y), R51.2
unnamed: IC7.94 (BOOT0), R56.2
unnamed: C48.2, IC7.14 (NRST)
unnamed: C41.2, IC7.12 (OSC_IN), Y1.1
unnamed: C45.2, IC7.13 (OSC_OUT), Y1.2
unnamed: IC7.37 (PB2), R63.1
unnamed: IC7.34 (PC5), R64.2, R65.1
unnamed: IC7.80 (PC12), LED2.1 (K)
unnamed: IC7.60 (PD13), TP25.1
unnamed: IC7.61 (PD14), TP26.1
unnamed: IC7.62 (PD15), TP27.1
unnamed: IC8.4 (ON/OFF), Q1.3 (C), Q2.3 (C), R57.2
unnamed: D14.1, IC8.2 (OUTPUT), L2.1
unnamed: C68.1, IC11.3 (VIN+), R70.2, TP14.1
unnamed: IC12.5 (2Y), R67.1
unnamed: JP1.1 (A), R53.1
unnamed: LED1.2 (A), R69.2
unnamed: LED2.2 (A), R60.2
unnamed: Q1.1 (B), R58.1, R73.2
unnamed: Q2.1 (B), R59.1

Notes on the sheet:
0V OFF 3V ON
0V OFF 3V OK
PWM DRIVERS
POWER SUPPLY
CONNECTORS
CURRENT SENSORS
RESOLVER
OVERCURRENT AND FAULT
STM32F103VCT6 MCU
GATE PSU ENABLE BUFFER
HIGH SIDE. NONINVERTING.
LOW SIDE. INVERTING.
HV SENSE SIGMA / DELTA
Board Detection
INPUTS DIGITAL / ANALOG
CANBUS
TEMP SENSORS
28-pin inverter connector 1 - Start 2 - Motortemp 1 3 - Throttle 1 4 - Throttle 2 5 - Cruise 6 - Brake 7 - +12v (kl30) 8 - Motortemp 2 9 10 11 12 13 - +15 Ignition (kl15) 14 - +5v Out 15 - CAN-L 16 - Motortemp 1 17 - Resolver SIN S4 18 - Resolver SIN S2 19 - Resolver EXC R2 20 21 22 - CAN-H 23 - Mo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
_- TO DO -_ * Link discharge Logic level or driver needed? * HS_Temp? Seems like CONN1 pin2 and pin4? * Should R27 be 10ohm? It's 10k in M3 * Should we keep the ESD protections on the board even if there is protection circuits on the OEM connector board? Do Not Mount?

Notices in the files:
Front/FDU_V1/FDU_V1.kicad_pcb:
©2026 D.MAGUIRE,J.HÜBNER,N.HEDLUND
